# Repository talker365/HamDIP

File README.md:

# HamDIP
Ham Radio based DIP for the NTC C.H.I.P. (chip)

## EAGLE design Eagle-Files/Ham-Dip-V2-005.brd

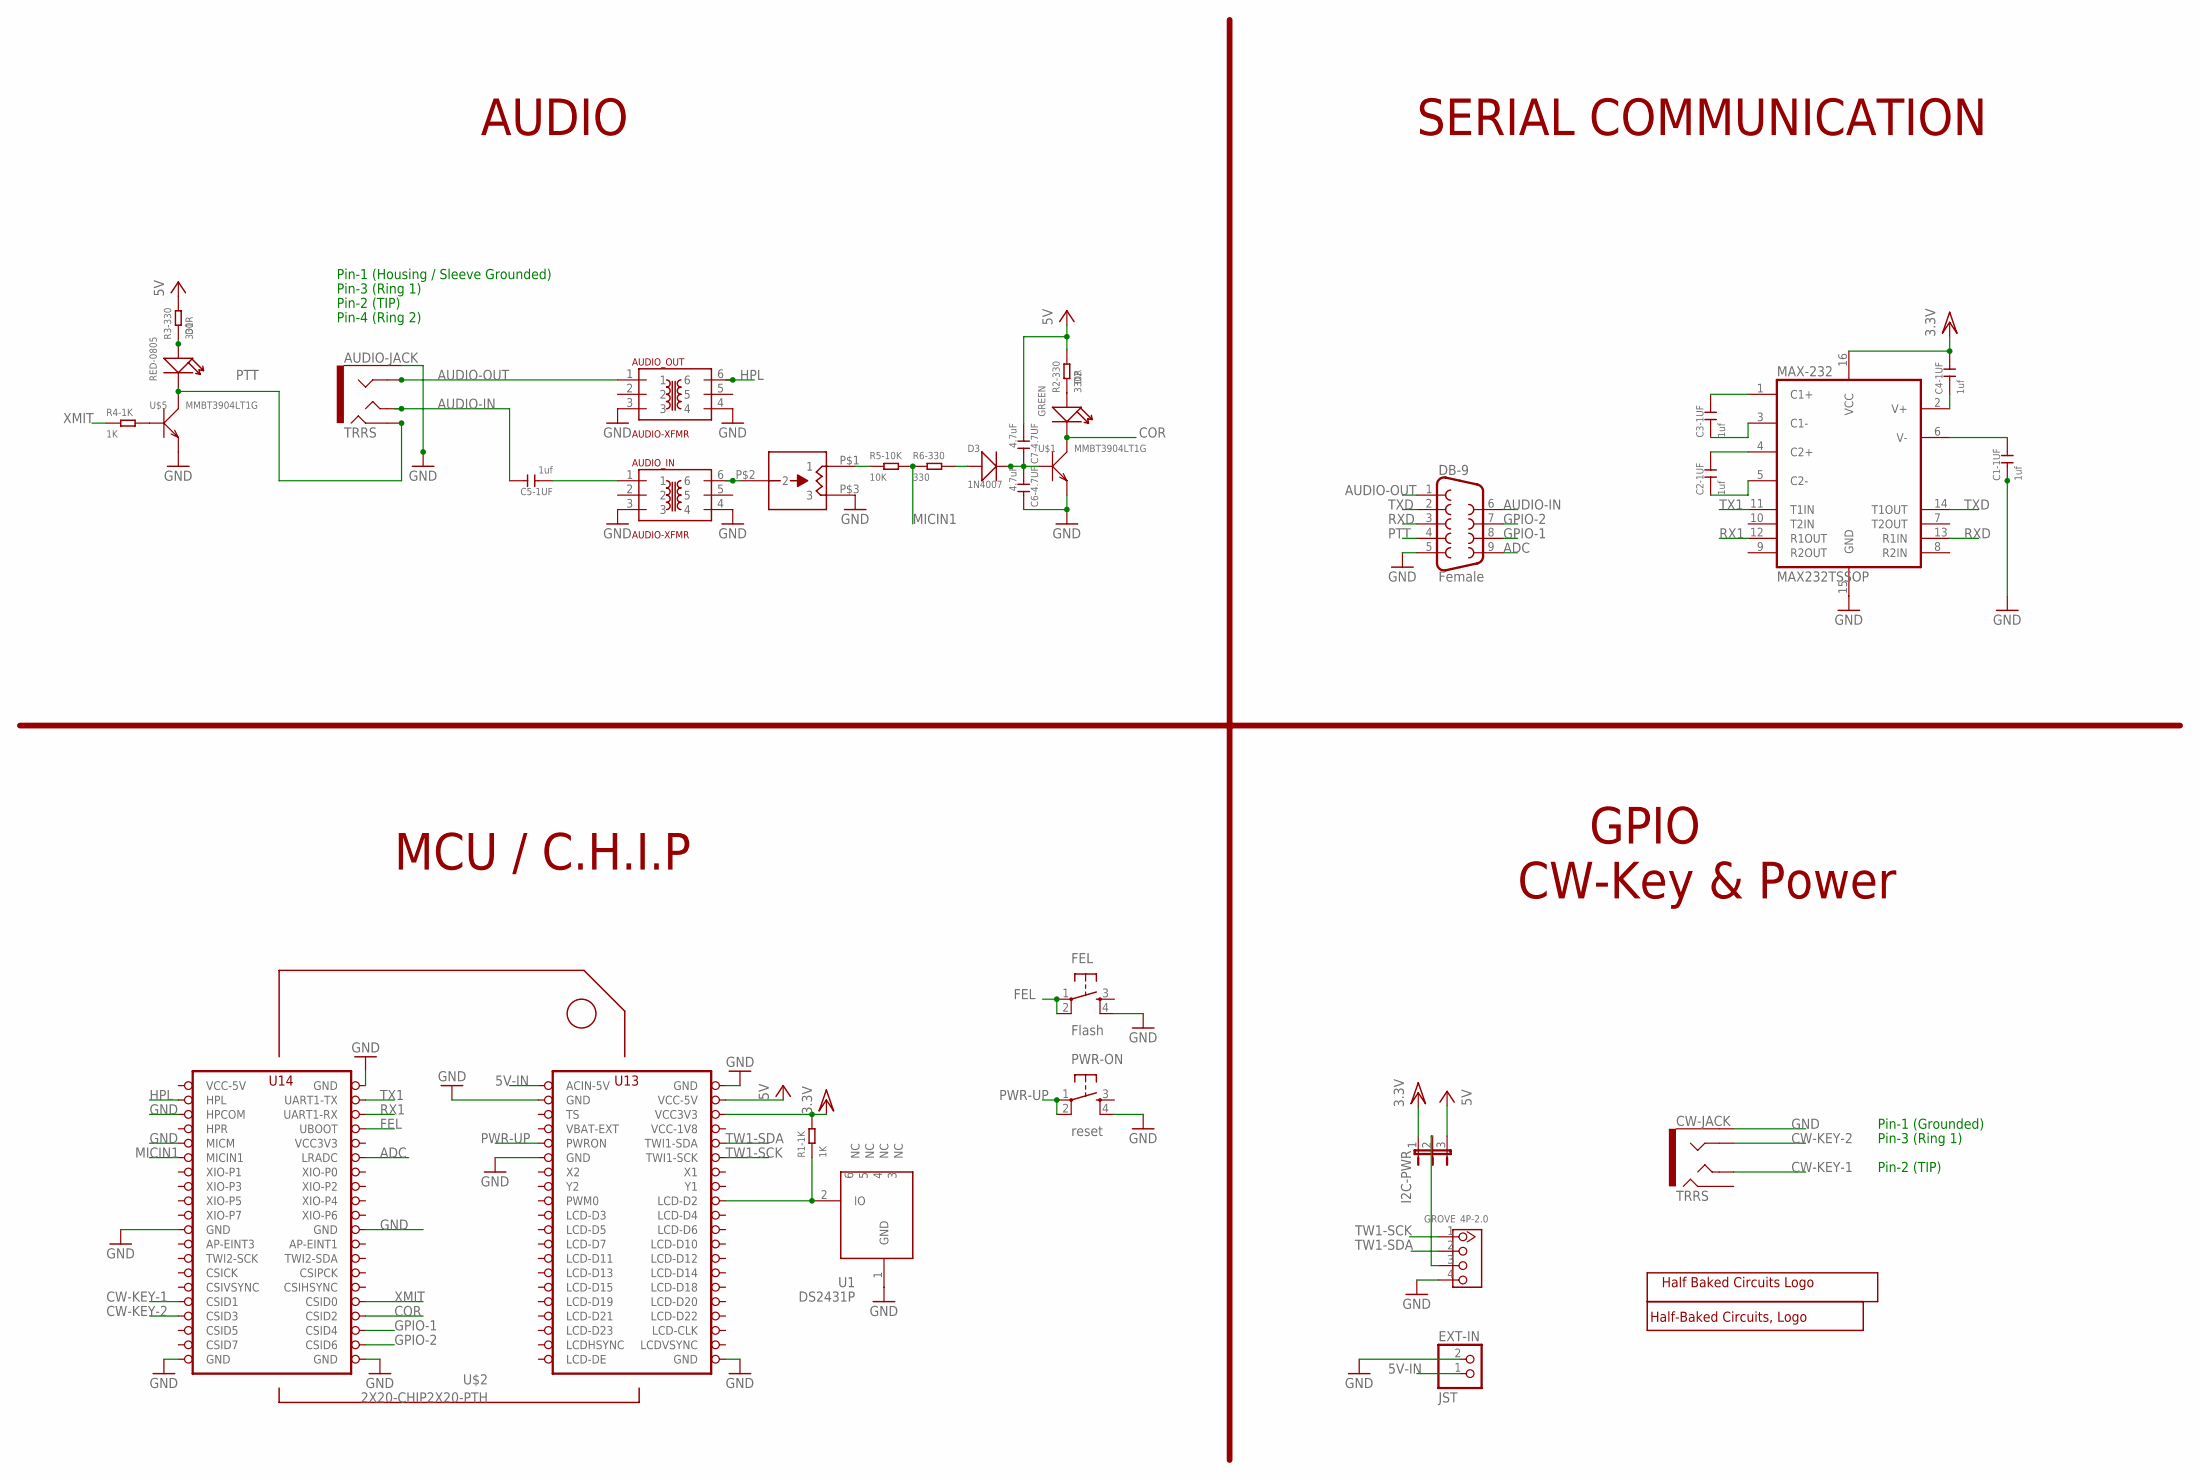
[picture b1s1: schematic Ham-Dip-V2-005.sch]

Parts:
AUDIO-JACK: TRRS; AUDIO-JACK-TRRS-SMD
AUDIO_IN: AUDIO-XFMR; SM-LP-5001
AUDIO_OUT: AUDIO-XFMR; SM-LP-5001
C1-1UF, C2-1UF, C3-1UF, C4-1UF, C5-1UF: 1uf; C0805
C6-4.7UF, C7-4.7UF: 4.7uF; C0805
CW-JACK: TRRS; AUDIO-JACK-TRRS-SMD
D1: RED-0805; LED-0805
D2: GREEN; LED-0805
D3: 1N4007; DO-214AC
DB-9: Female; DB9
EXT-IN: JST; JST-PH-2-THM
FEL: Flash; TACTILE_SWITCH_SMD
GROVE: 4P-2.0; HW4-2.0
I2C-PWR: JP2E; JP2
MAX-232: MAX232TSSOP; TSSOP16
MIC-LVL: 1K; TC33X
PWR-ON: reset; TACTILE_SWITCH_SMD
R1-1K, R4-1K: 1K; R0805
R2-330, R3-330: 330R; R0805
R5-10K: 10K; R0805
R6-330: 330; R0805
U1: DS2431P; TSOC6
U$1, U$5: MMBT3904LT1G; SOT-23
U$2: 2X20-CHIP2X20-PTH; 2X20CHIP-TH
U$3: HBC-LOGO
U$4: HAM-DIP

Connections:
5V-IN: EXT-IN.1 (2), U$2.CHG-IN (ACIN-5V)
ADC: DB-9.9, U$2.LRADC
AUDIO-IN: AUDIO-JACK.TIP, C5-1UF.2, DB-9.6
AUDIO-OUT: AUDIO-JACK.RING1, AUDIO_OUT.1, DB-9.1
COR: D2.-, U$1.3 (C), U$2.CSID2
CW-KEY-1: CW-JACK.TIP, U$2.CSID1
CW-KEY-2: CW-JACK.RING1, U$2.CSID3
FEL: FEL.1, FEL.2, U$2.FEL (UBOOT)
GND: AUDIO-JACK.EARTH, AUDIO_IN.3, AUDIO_IN.4, AUDIO_OUT.3, AUDIO_OUT.4, C1-1UF.1, C6-4.7UF.2, CW-JACK.EARTH, DB-9.5, EXT-IN.2 (1), FEL.4, GROVE.4, MAX-232.15 (GND), MIC-LVL.P$3 (3), PWR-ON.4, U1.1 (GND), U$1.2 (E), U$2.GND@1 (GND), U$2.GND@2 (GND), U$2.GND@3 (GND), U$2.GND@4 (GND), U$2.GND@5 (GND), U$2.GND@6 (GND), U$2.GND@7 (GND), U$2.GND@8 (GND), U$2.GND@10 (GND), U$2.HPCOM, U$2.MICM, U$5.2 (E)
GPIO-1: DB-9.8, U$2.CSID4
GPIO-2: DB-9.7, U$2.CSID6
HPL: AUDIO_OUT.6, U$2.HPL
IN: AUDIO_IN.1, C5-1UF.1
MICIN1: R5-10K.2, R6-330.1, U$2.MICIN1
unnamed: D1.+, R3-330.1
unnamed: MIC-LVL.P$1 (1), R5-10K.1
unnamed: AUDIO_IN.6, MIC-LVL.P$2 (2)
unnamed: GROVE.3, I2C-PWR.2
unnamed: C4-1UF.1, MAX-232.2 (V+)
unnamed: R1-1K.1, U1.2 (IO), U$2.LCD-D2
unnamed: R4-1K.2, U$5.1 (B)
unnamed: D2.+, R2-330.1
unnamed: C6-4.7UF.1, C7-4.7UF.2, D3.2 (-), U$1.1 (B)
unnamed: C1-1UF.2, MAX-232.6 (V-)
unnamed: D3.1 (+), R6-330.2
unnamed: C3-1UF.2, MAX-232.1 (C1+)
unnamed: C2-1UF.2, MAX-232.4 (C2+)
unnamed: C3-1UF.1, MAX-232.3 (C1-)
unnamed: C2-1UF.1, MAX-232.5 (C2-)
PTT: AUDIO-JACK.RING2, D1.-, DB-9.4, U$5.3 (C)
PWR-UP: PWR-ON.1, PWR-ON.2, U$2.PWRON
RX1: MAX-232.12 (R1OUT), U$2.UART1-RX
RXD: DB-9.3, MAX-232.13 (R1IN)
TW1-SCK: GROVE.1, U$2.TWI1-SCK
TW1-SDA: GROVE.2, U$2.TWI1-SDA
TX1: MAX-232.11 (T1IN), U$2.UART1-TX
TXD: DB-9.2, MAX-232.14 (T1OUT)
VCC: C7-4.7UF.1, I2C-PWR.3, R2-330.2, R3-330.2, U$2.VCC5V@0 (VCC-5V)
VCC3V3: U$2.VCC3V3@1 (VCC3V3)
VCC-1V8: U$2.VCC1V8 (VCC-1V8)
VCC-5V: U$2.VCC5V@1 (VCC-5V)
VCC/2: C4-1UF.2, I2C-PWR.1, MAX-232.16 (VCC), R1-1K.2, U$2.VCC3V3
XMIT: R4-1K.1, U$2.CSID0

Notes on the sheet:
Pin-1 (Grounded)
Pin-3 (Ring 1)
Pin-2 (TIP)
Pin-1 (Housing / Sleeve Grounded)
Pin-4 (Ring 2)
AUDIO
MCU / C.H.I.P
SERIAL COMMUNICATION
GPIO CW-Key & Power

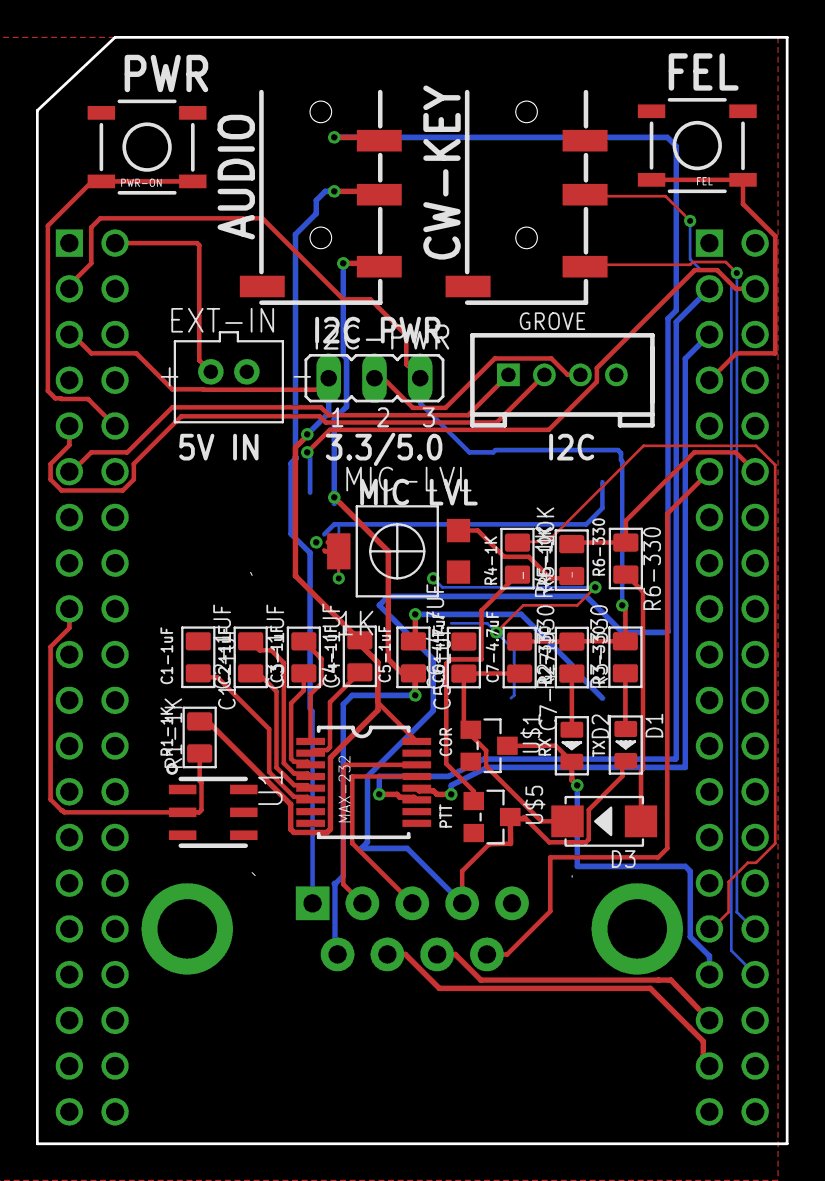
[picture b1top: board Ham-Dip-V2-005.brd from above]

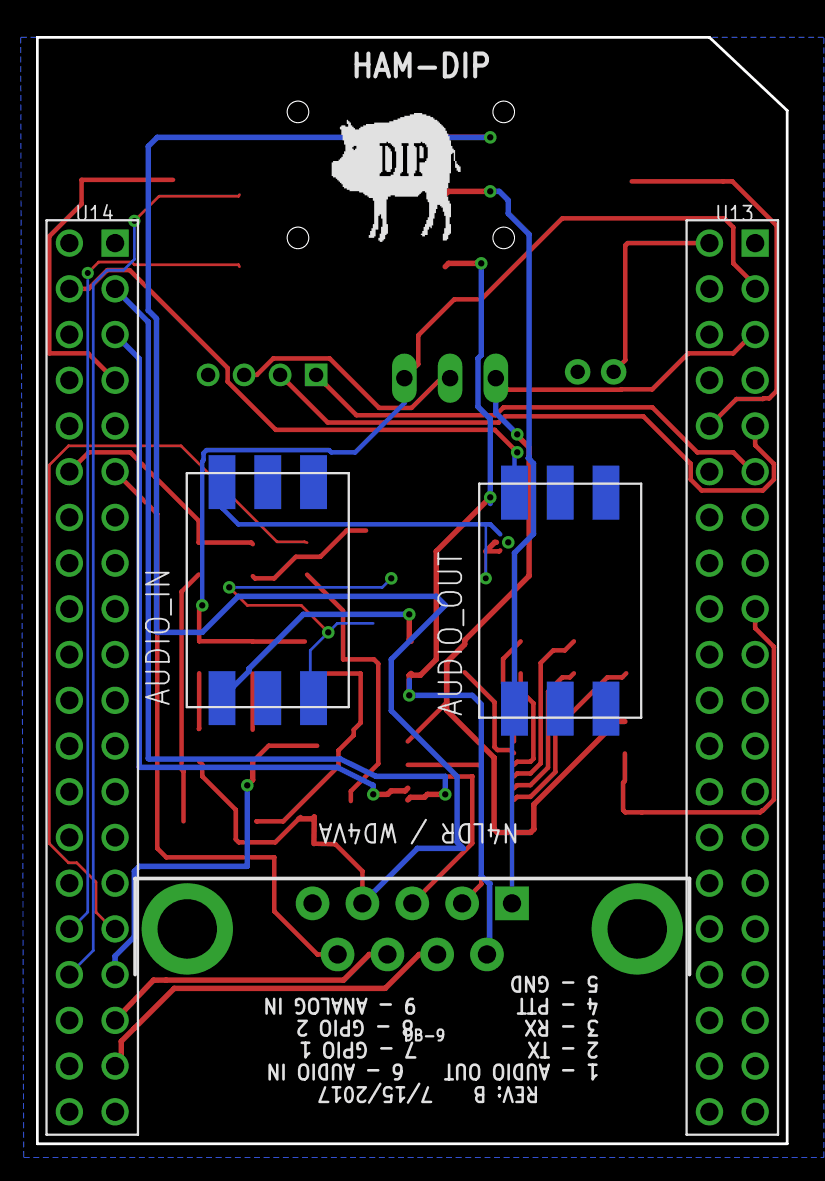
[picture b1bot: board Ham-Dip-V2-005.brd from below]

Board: 2 copper layers, 41.7 x 61.5 mm, 34 parts (4 on the bottom side), 40 nets.

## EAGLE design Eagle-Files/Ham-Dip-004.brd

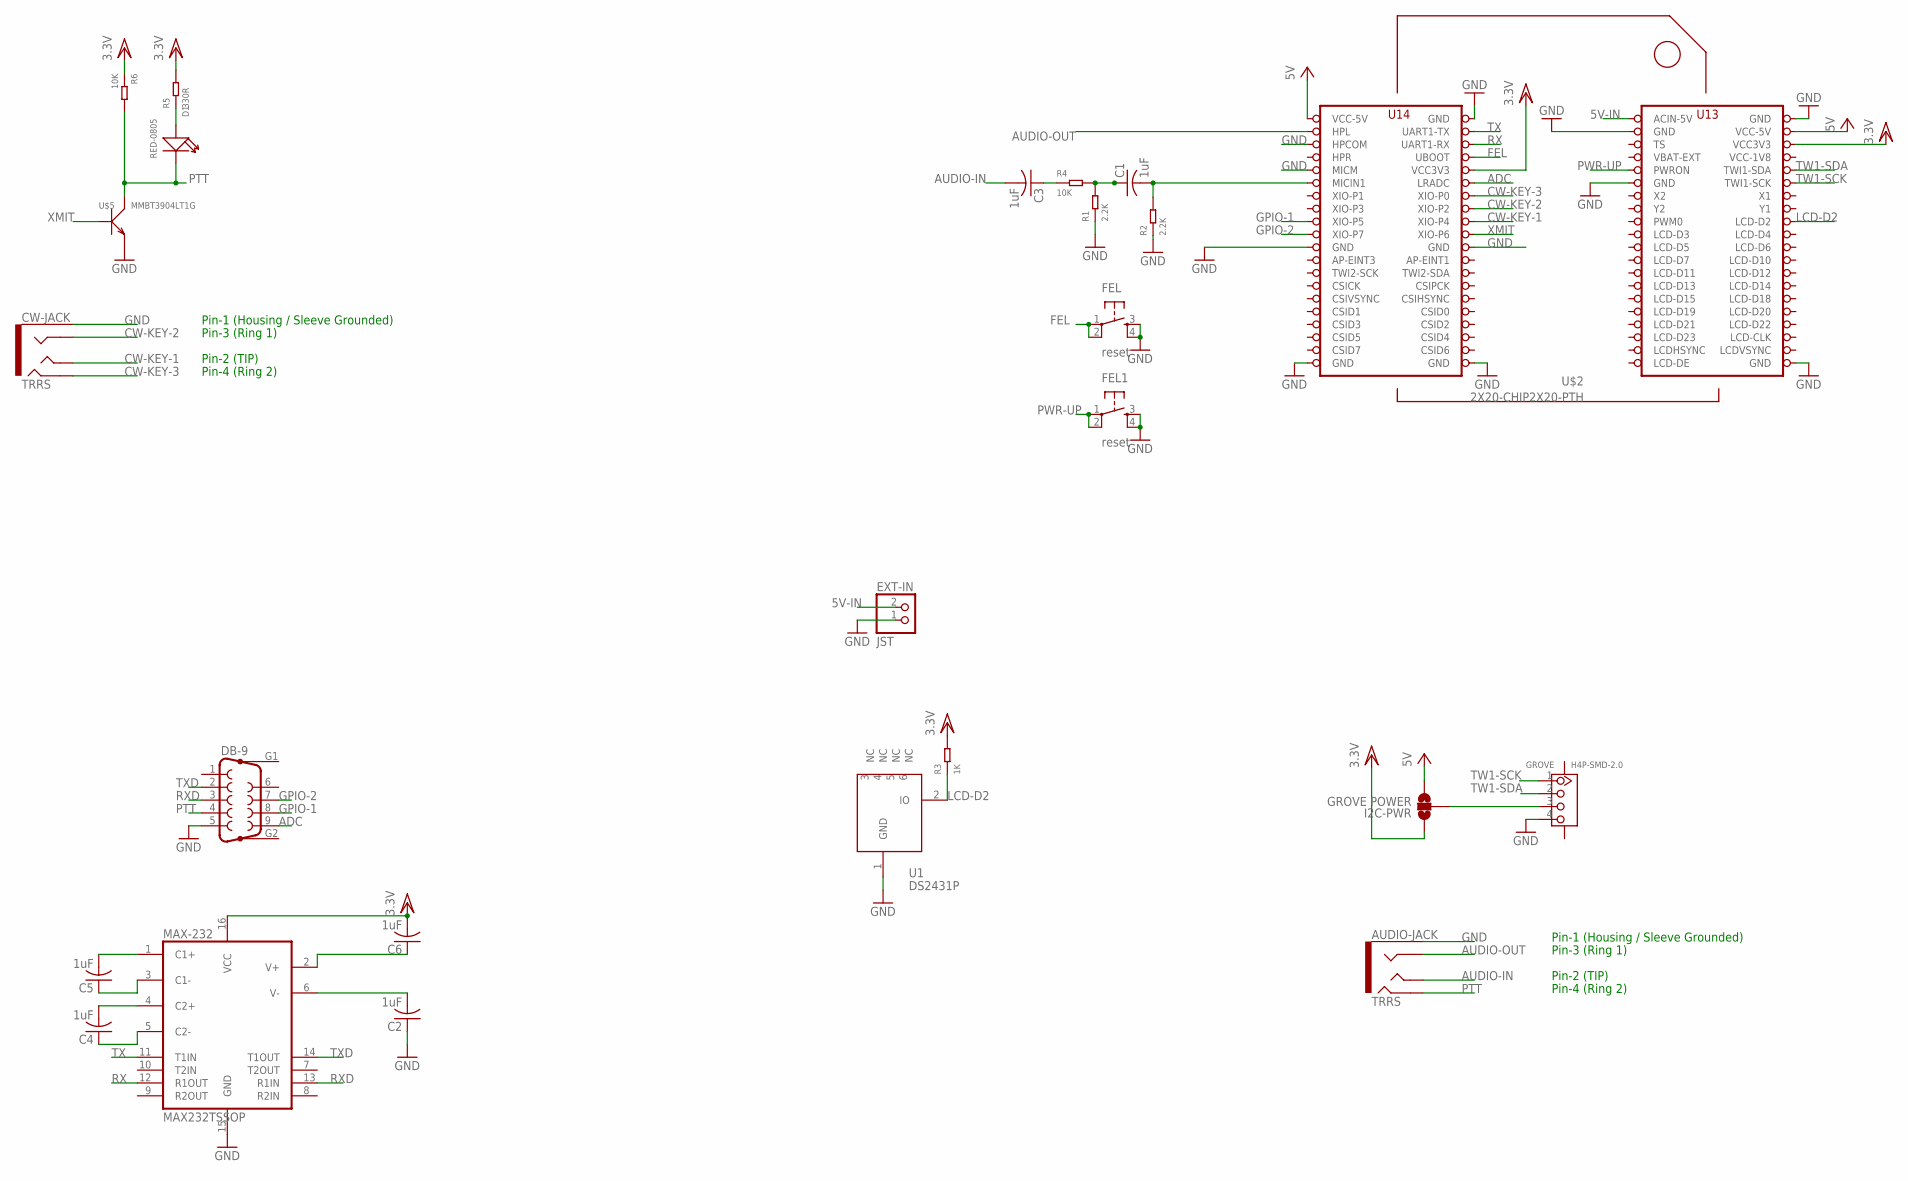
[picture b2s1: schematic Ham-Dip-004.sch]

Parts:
AUDIO-JACK: TRRS; AUDIO-JACK-TRRS-SMD
C1, C2, C3, C4, C5, C6: 1uF; C0805
CW-JACK: TRRS; AUDIO-JACK-TRRS-SMD
D1: RED-0805; LED-0805
DB-9: F09HP
EXT-IN: JST; JST-PH-2-SMT
FEL, FEL1: reset; TACTILE_SWITCH_SMD
GROVE: H4P-SMD-2.0; HW4-SMD-2.0
I2C-PWR: GROVE POWER; SMD_SJ_3WAY_OPEN
MAX-232: MAX232TSSOP; TSSOP16
R1, R2: 2.2K; R0805
R3: 1K; R0805
R4, R6: 10K; R0805
R5: 330R; R0805
U1: DS2431P; TSOC6
U$2: 2X20-CHIP2X20-PTH; 2X20CHIP-TH
U$5: MMBT3904LT1G; SOT-23

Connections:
5V-IN: EXT-IN.2 (1), U$2.CHG-IN (ACIN-5V)
ADC: DB-9.9, U$2.LRADC
AUDIO-IN: AUDIO-JACK.TIP, C3.2
AUDIO-OUT: AUDIO-JACK.RING1, U$2.HPL
CW-KEY-1: CW-JACK.TIP, U$2.XIO-P4
CW-KEY-2: CW-JACK.RING1, U$2.XIO-P2
CW-KEY-3: CW-JACK.RING2, U$2.XIO-P0
FEL: FEL.1, FEL.2, U$2.FEL (UBOOT)
GND: AUDIO-JACK.EARTH, C2.1, CW-JACK.EARTH, DB-9.5, EXT-IN.1 (2), FEL.3, FEL.4, FEL1.3, FEL1.4, GROVE.4, MAX-232.15 (GND), R1.1, R2.1, U1.1 (GND), U$2.GND@1 (GND), U$2.GND@2 (GND), U$2.GND@3 (GND), U$2.GND@4 (GND), U$2.GND@5 (GND), U$2.GND@6 (GND), U$2.GND@7 (GND), U$2.GND@8 (GND), U$2.GND@10 (GND), U$2.HPCOM, U$2.MICM, U$5.2 (E)
GPIO-1: DB-9.8, U$2.XIO-P5
GPIO-2: DB-9.7, U$2.XIO-P7
LCD-D2: R3.1, U1.2 (IO), U$2.LCD-D2
MIC-IN: C1.2, R2.2, U$2.MICIN1
unnamed: D1.+, R5.1
unnamed: C3.1, R4.1
unnamed: C1.1, R1.2, R4.2
unnamed: GROVE.3, I2C-PWR.2
unnamed: C6.1, MAX-232.2 (V+)
unnamed: C2.2, MAX-232.6 (V-)
unnamed: C5.2, MAX-232.1 (C1+)
unnamed: C4.2, MAX-232.4 (C2+)
unnamed: C5.1, MAX-232.3 (C1-)
unnamed: C4.1, MAX-232.5 (C2-)
PTT: AUDIO-JACK.RING2, D1.-, DB-9.4, R6.2, U$5.3 (C)
PWR-UP: FEL1.1, FEL1.2, U$2.PWRON
RX: MAX-232.12 (R1OUT), U$2.UART1-RX
RXD: DB-9.3, MAX-232.13 (R1IN)
TW1-SCK: GROVE.1, U$2.TWI1-SCK
TW1-SDA: GROVE.2, U$2.TWI1-SDA
TX: MAX-232.11 (T1IN), U$2.UART1-TX
TXD: DB-9.2, MAX-232.14 (T1OUT)
VCC: I2C-PWR.3, U$2.VCC5V@0 (VCC-5V), U$2.VCC5V@1 (VCC-5V)
VCC-1V8: U$2.VCC1V8 (VCC-1V8)
VCC/2: C6.2, I2C-PWR.1, MAX-232.16 (VCC), R3.2, R5.2, R6.1, U$2.VCC3V3, U$2.VCC3V3@1 (VCC3V3)
XMIT: U$2.XIO-P6, U$5.1 (B)

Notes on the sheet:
Pin-1 (Housing / Sleeve Grounded)
Pin-3 (Ring 1)
Pin-2 (TIP)
Pin-4 (Ring 2)

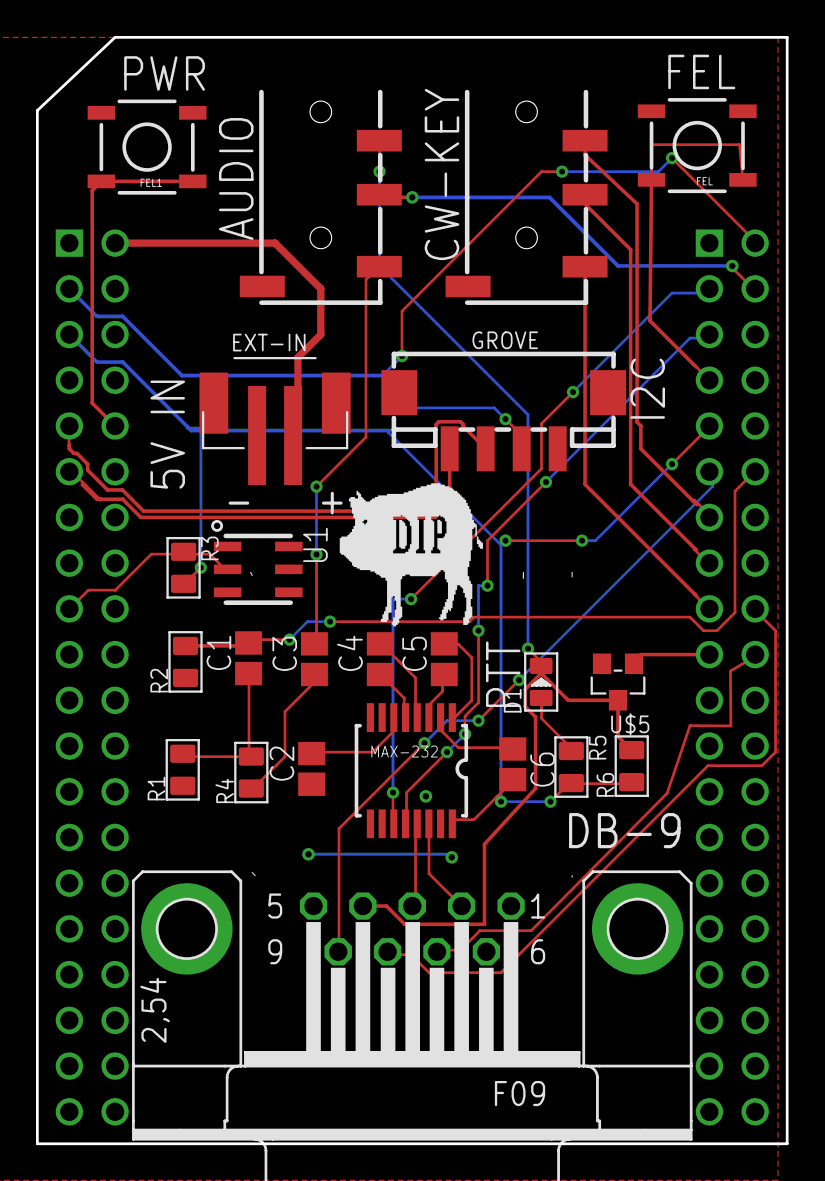
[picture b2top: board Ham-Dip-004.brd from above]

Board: 2 copper layers, 41.7 x 61.5 mm, 25 parts (1 on the bottom side), 34 nets.

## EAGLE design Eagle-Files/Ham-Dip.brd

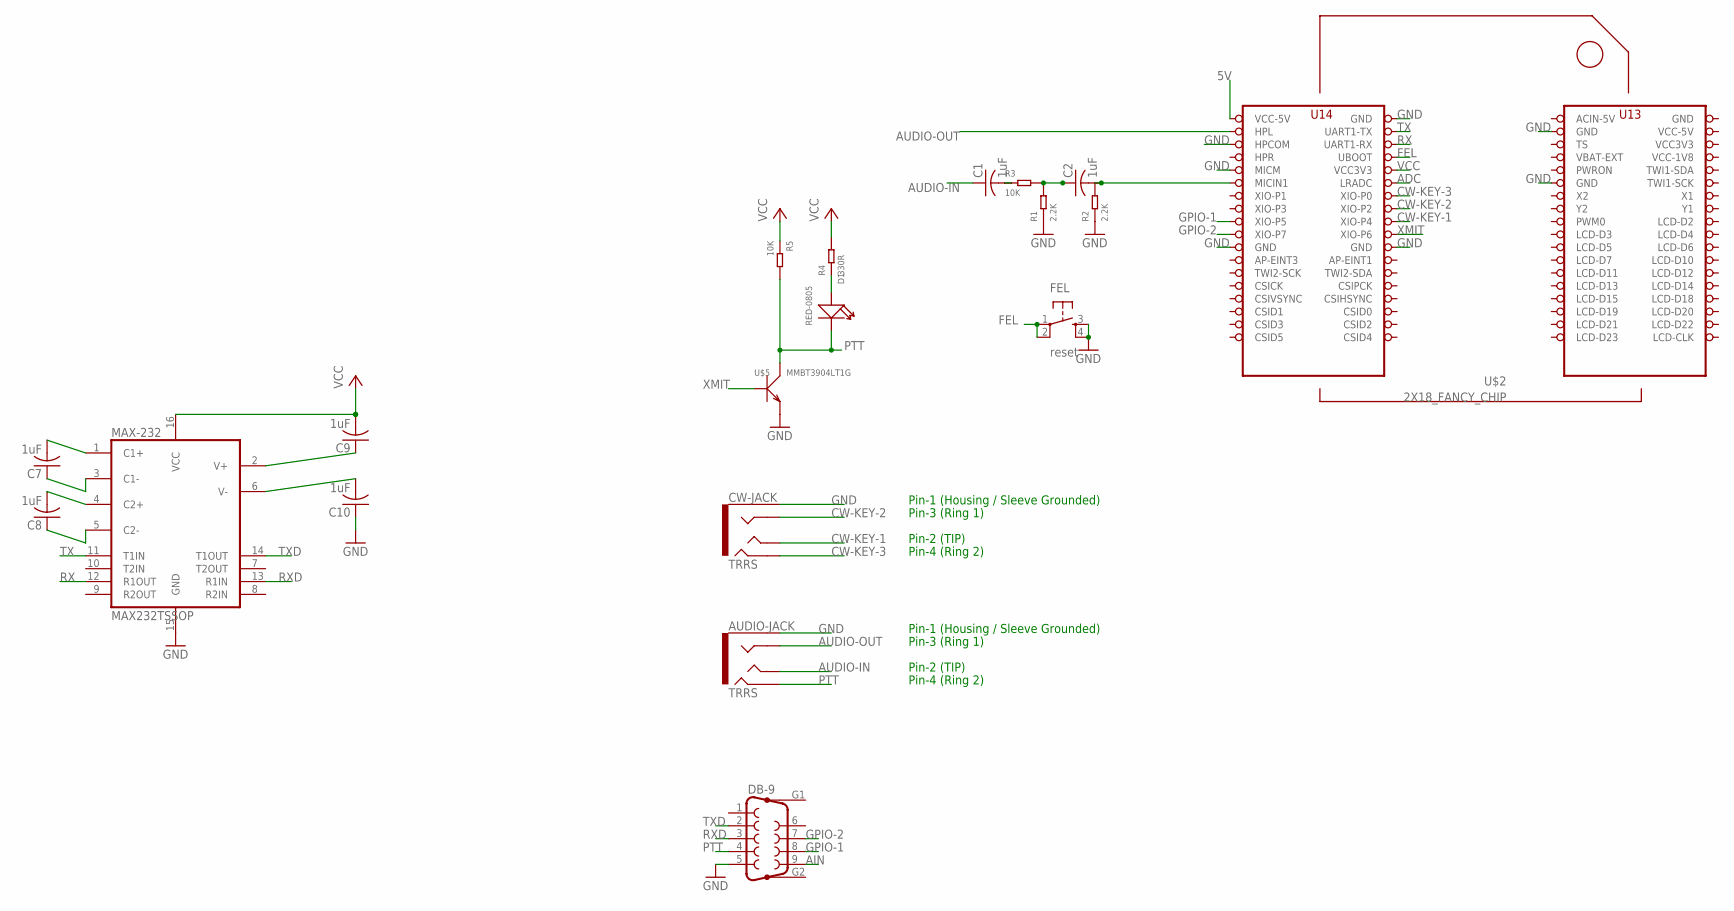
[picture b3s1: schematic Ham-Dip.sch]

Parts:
AUDIO-JACK: TRRS; AUDIO-JACK-TRRS-SMD
C1, C2, C7, C8, C9, C10: 1uF; C0805
CW-JACK: TRRS; AUDIO-JACK-TRRS-SMD
D1: RED-0805; LED-0805
DB-9: F09HP
FEL: reset; TACTILE_SWITCH_SMD
MAX-232: MAX232TSSOP; TSSOP16
R1, R2: 2.2K; R0805
R3, R5: 10K; R0805
R4: 330R; R0805
U$2: 2X18_FANCY_CHIP; 2X18_FANCY_EDGE_CHIP_TH
U$5: MMBT3904LT1G; SOT-23

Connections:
5V: U$2.72 (VCC-5V)
ADC: U$2.61 (LRADC)
AIN: DB-9.9
AUDIO-IN: AUDIO-JACK.TIP, C1.1
AUDIO-OUT: AUDIO-JACK.RING1, U$2.70 (HPL)
CW-KEY-1: CW-JACK.TIP, U$2.55 (XIO-P4)
CW-KEY-2: CW-JACK.RING1, U$2.57 (XIO-P2)
CW-KEY-3: CW-JACK.RING2, U$2.59 (XIO-P0)
FEL: FEL.1, FEL.2, U$2.65 (UBOOT)
GND: AUDIO-JACK.EARTH, C10.1, CW-JACK.EARTH, DB-9.5, FEL.3, FEL.4, MAX-232.15 (GND), R1.1, R2.1, U$2.26 (GND), U$2.34 (GND), U$2.35 (GND), U$2.51 (GND), U$2.52 (GND), U$2.64 (MICM), U$2.68 (HPCOM), U$2.71 (GND), U$5.2 (E)
GPIO-1: DB-9.8, U$2.56 (XIO-P5)
GPIO-2: DB-9.7, U$2.54 (XIO-P7)
MIC-IN: C2.2, R2.2, U$2.62 (MICIN1)
unnamed: D1.+, R4.1
unnamed: C1.2, R3.1
unnamed: C2.1, R1.2, R3.2
unnamed: C9.1, MAX-232.2 (V+)
unnamed: C10.2, MAX-232.6 (V-)
unnamed: C7.2, MAX-232.1 (C1+)
unnamed: C8.2, MAX-232.4 (C2+)
unnamed: C7.1, MAX-232.3 (C1-)
unnamed: C8.1, MAX-232.5 (C2-)
PTT: AUDIO-JACK.RING2, D1.-, DB-9.4, R5.2, U$5.3 (C)
RX: MAX-232.12 (R1OUT), U$2.67 (UART1-RX)
RXD: DB-9.3, MAX-232.13 (R1IN)
TX: MAX-232.11 (T1IN), U$2.69 (UART1-TX)
TXD: DB-9.2, MAX-232.14 (T1OUT)
VCC: C9.2, MAX-232.16 (VCC), R4.2, R5.1, U$2.63 (VCC3V3)
VCC3V3: U$2.31 (VCC3V3)
VCC-1V8: U$2.29 (VCC-1V8)
VCC-5V: U$2.33 (VCC-5V)
XMIT: U$2.53 (XIO-P6), U$5.1 (B)

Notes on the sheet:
Pin-1 (Housing / Sleeve Grounded)
Pin-3 (Ring 1)
Pin-2 (TIP)
Pin-4 (Ring 2)

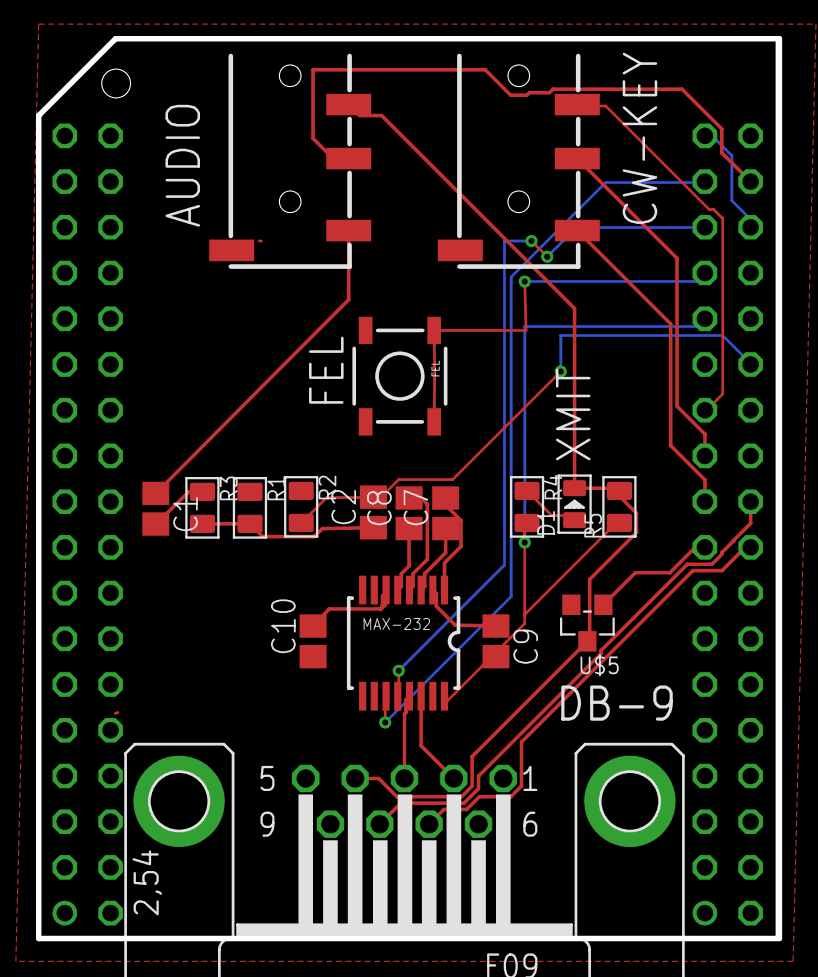
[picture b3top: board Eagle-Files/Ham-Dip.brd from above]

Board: 2 copper layers, 41.1 x 50.0 mm, 19 parts (0 on the bottom side), 26 nets.

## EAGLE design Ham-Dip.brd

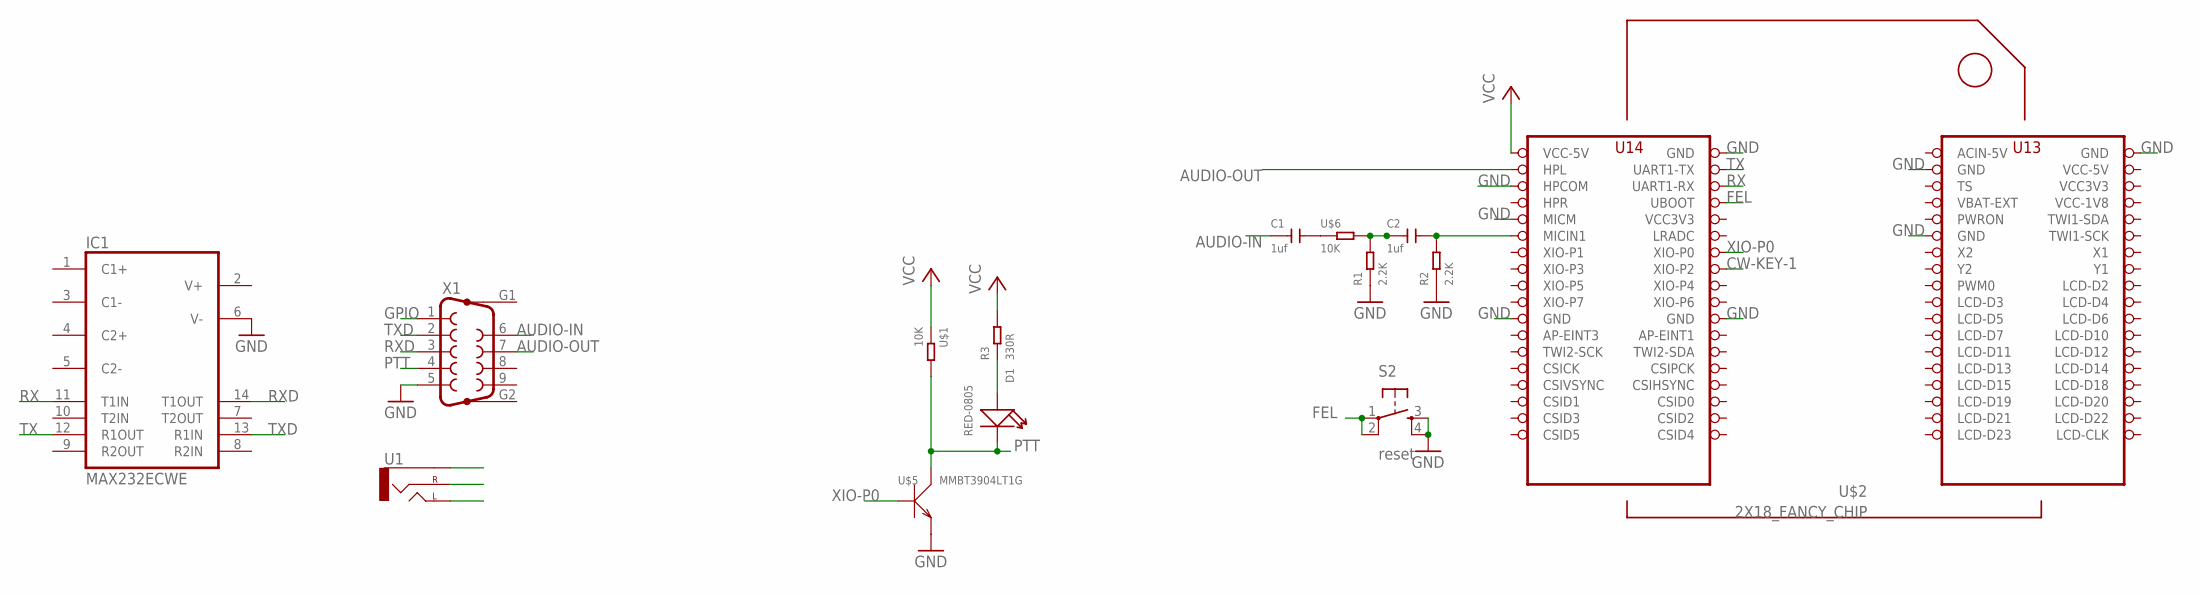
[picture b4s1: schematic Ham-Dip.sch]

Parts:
C1, C2: 1uf; C0603
D1: RED-0805; LED-0805
IC1: MAX232ECWE; SO16L
R1, R2: 2.2K; R0805
R3: 330R; R0805
S2: reset; TACTILE_SWITCH_SMD
U1: AUDIO-JACKPTH; AUDIO-JACK
U$1, U$6: 10K; R0805
U$2: 2X18_FANCY_CHIP; 2X18_FANCY_EDGE_CHIP_TH
U$5: MMBT3904LT1G; SOT-23
X1: F09HP

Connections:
$N$2: IC1.6 (V-), IC1.15 (GND), R1.1, R2.1, S2.3, S2.4, U1.SLEEVE, U$2.26 (GND), U$2.34 (GND), U$2.35 (GND), U$2.51 (GND), U$2.52 (GND), U$2.64 (MICM), U$2.68 (HPCOM), U$2.71 (GND), U$5.2 (E), X1.5
AUDIO-IN: C1.1, X1.6
AUDIO-OUT: U$2.70 (HPL), X1.7
CW-KEY-1: U1.RING (RIGHT), U$2.57 (XIO-P2)
CW-KEY-2: U1.TIP (LEFT)
FEL: S2.1, S2.2, U$2.65 (UBOOT)
GPIO: X1.1
MIC-IN: C2.2, R2.2, U$2.62 (MICIN1)
unnamed: D1.+, R3.1
unnamed: C1.2, U$6.1
unnamed: C2.1, R1.2, U$6.2
PTT: D1.-, U$1.2, U$5.3 (C), X1.4
RX: IC1.11 (T1IN), U$2.67 (UART1-RX)
RXD: IC1.14 (T1OUT), X1.3
TX: IC1.12 (R1OUT), U$2.69 (UART1-TX)
TXD: IC1.13 (R1IN), X1.2
VCC: IC1.16 (VCC), R3.2, U$1.1, U$2.72 (VCC-5V)
VCC3V3: U$2.31 (VCC3V3), U$2.63 (VCC3V3)
VCC-1V8: U$2.29 (VCC-1V8)
VCC-5V: U$2.33 (VCC-5V)
XIO-P0: U$2.59 (XIO-P0), U$5.1 (B)

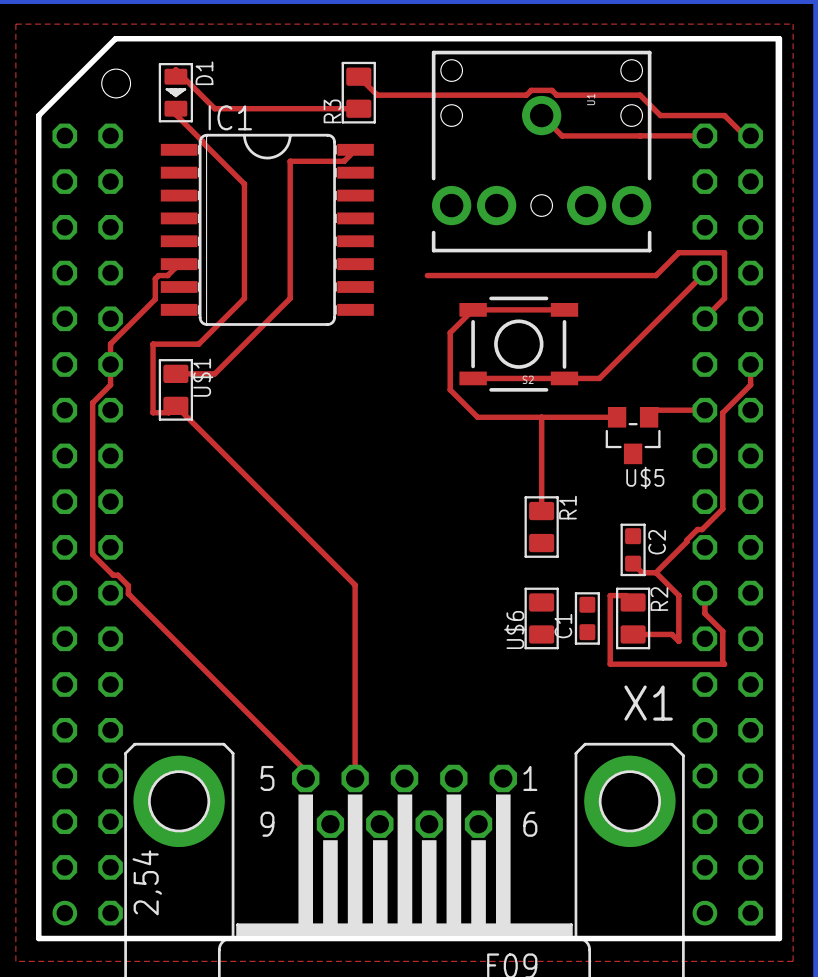
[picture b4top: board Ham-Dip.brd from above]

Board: 2 copper layers, 41.1 x 50.0 mm, 14 parts (0 on the bottom side), 17 nets.

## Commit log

2017-06-03 Initial Load
2017-06-03 Updated Drawings.
    Includes Files to Generate 3D Rendering.
2017-06-03 Corrected Wiring on TRRS Jack
2017-06-05 Added 3D Rendering Files to Git
2017-06-10 Updated Changes
2017-07-19 Half Baked Circuits Logo Draft 1
2017-07-21 new logo for boards
2017-07-21 latest Changes
2017-07-21 Added Sensor Template & Library
2017-07-21 Revised Sensor Template
2017-07-22 model update
2017-07-23 added 1-wire library
2019-09-05 Update Eagle-Files/Ham-Dip-V2-001.s##

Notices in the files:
parts and their libraries:
SparkFun-Electromechanical: Licensing: CC v3.0 Share-Alike You are welcome to use this library for commercial purposes.
